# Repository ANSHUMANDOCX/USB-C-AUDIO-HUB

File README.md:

# USB C AUDIO + USB HUB

## About
This is a USB C HUB along with a Audio Out/In port. This design uses PCM2912A along with SL2.1A 

- It has 3 downstream USB-C ports and 1 USB-C input so we can connect any desired length of cable we want to use with it
- TRRS audio jack for headphones with integrated microphone along with a mute/unmute switch built into the hub 
## Usage guide
- using it is as simple as it can be you just need to plug into the single usb C on the side and connected it to your device there are no driver needed 
- It doesnt need any firmware flashing 
- Its compatible with windows and linux 
## Assembly guide
All you need to do is place the PCB at the base plate align the holes and place the Body on top of it and screw the two parts using M2.5x6 or M2.5x8 countersunk screws.
## Parts used 
- TRRS Audio port
- USB C ports 
- PCM2912A
- SL2.1A
## Features
- USB 2.0 Full-Speed audio interface
- Stereo DAC output for headphones
- Microphone input with bias supply
- Integrated USB hub for multiple downstream devices
## PCB SCHEMATIC AND CAD

## Build 

https://drive.google.com/file/d/1LVbVrCVM0A2IdHVQDUf04vvttPNs0SB3/view?usp=sharing

## BOM
| SL NO | DESCRIPTION                                                | SUPPLIER    | PRICE |
|------|------------------------------------------------------------|------------|-------|
| 1 | [LCSC BOM items](https://github.com/ANSHUMANDOCX/USB-C-AUDIO-HUB/blob/main/PCB/BOM.csv) | LCSC | $22 |
| 2 | PCB and Stencil | JLCPCB | $16 |
| 3 | Screws and Heatset Inserts | Only Screws | $2 |
|4| [Solder Paste](https://www.flipkart.com/babatools-rl-403-solder-paste-10cc-1-w-simple/p/itm13022305a7dd0?pid=SOIGP28DYHUXUUF6&lid=LSTSOIGP28DYHUXUUF6AXDR0B&marketplace=FLIPKART&cmpid=content_soldering-iron_23274603117_g_8965229628_gmc_pla&tgi=sem,1,G,11214002,g,search,,784823478926,,,,c,,,,,,,&&cmpid=content_23274603117_gmc_pla&gad_campaignid=23274603117) | Flipkart| 4$|
|  | **TOTAL** |  | **$44** |

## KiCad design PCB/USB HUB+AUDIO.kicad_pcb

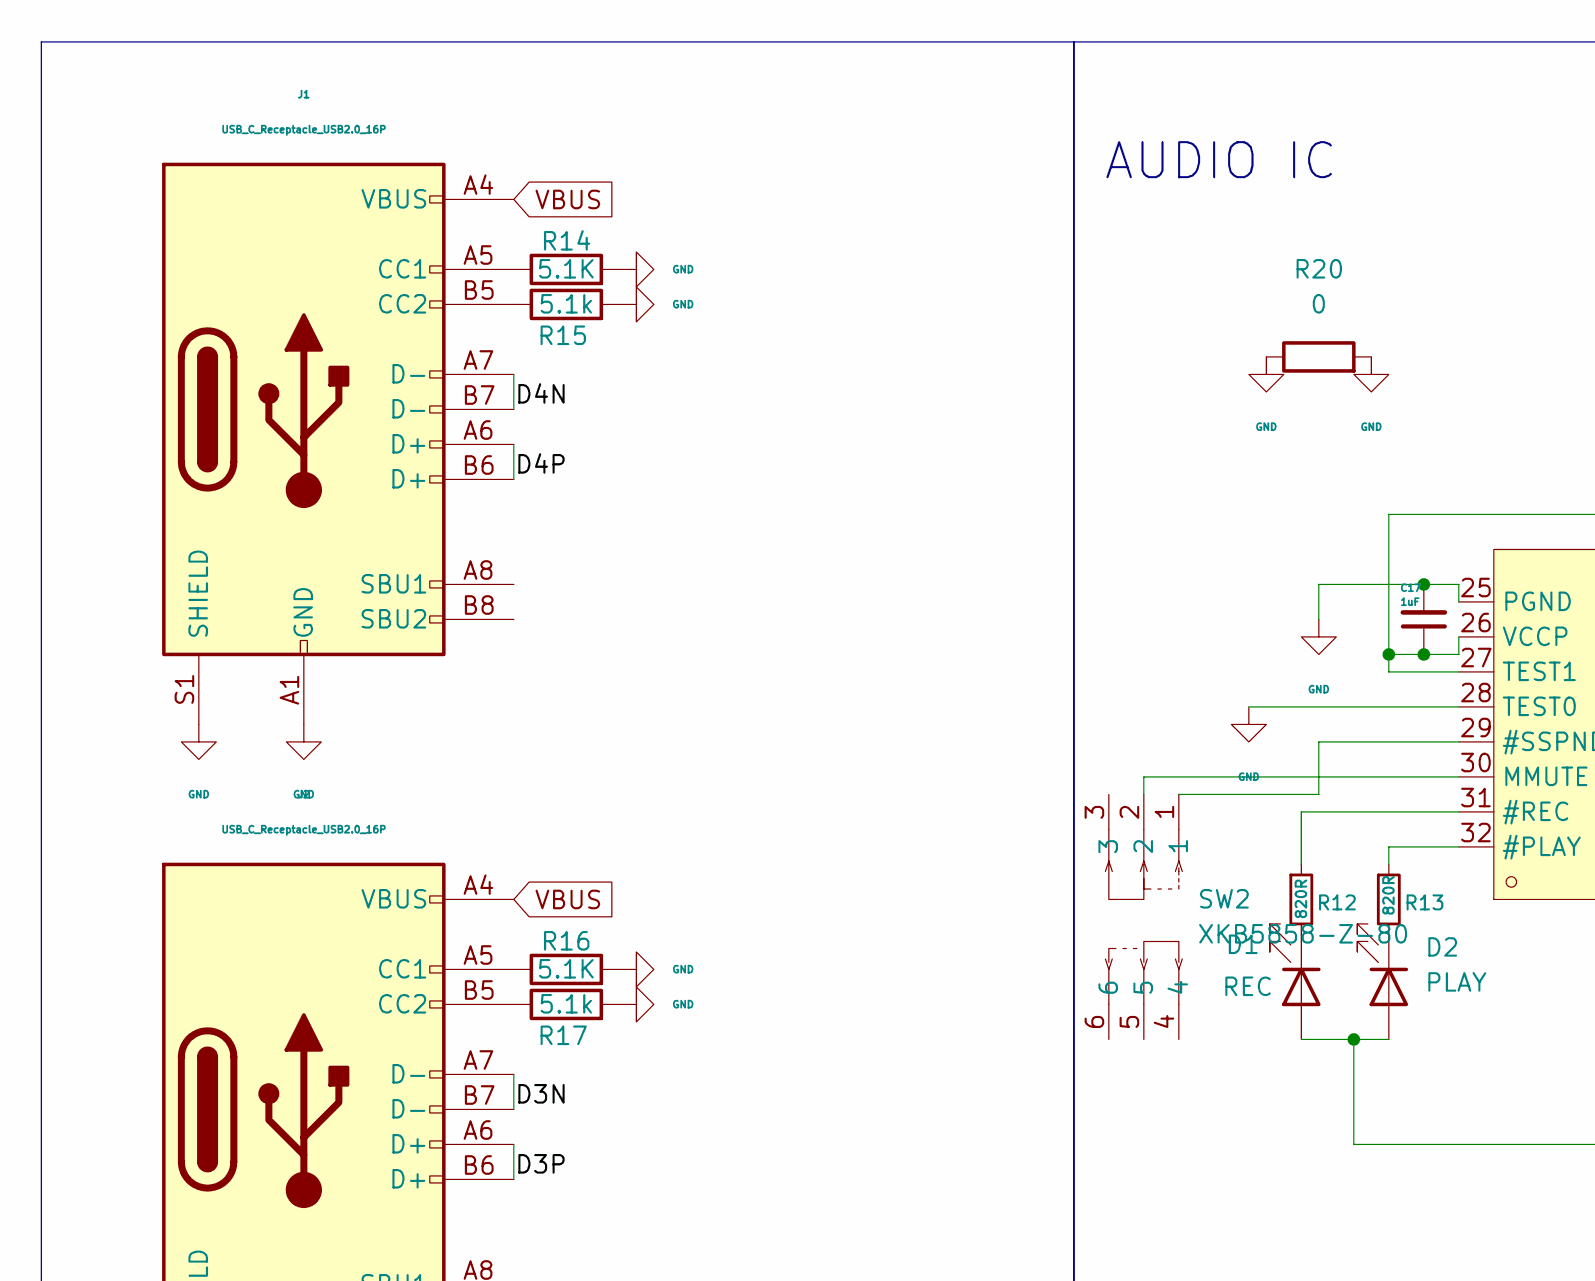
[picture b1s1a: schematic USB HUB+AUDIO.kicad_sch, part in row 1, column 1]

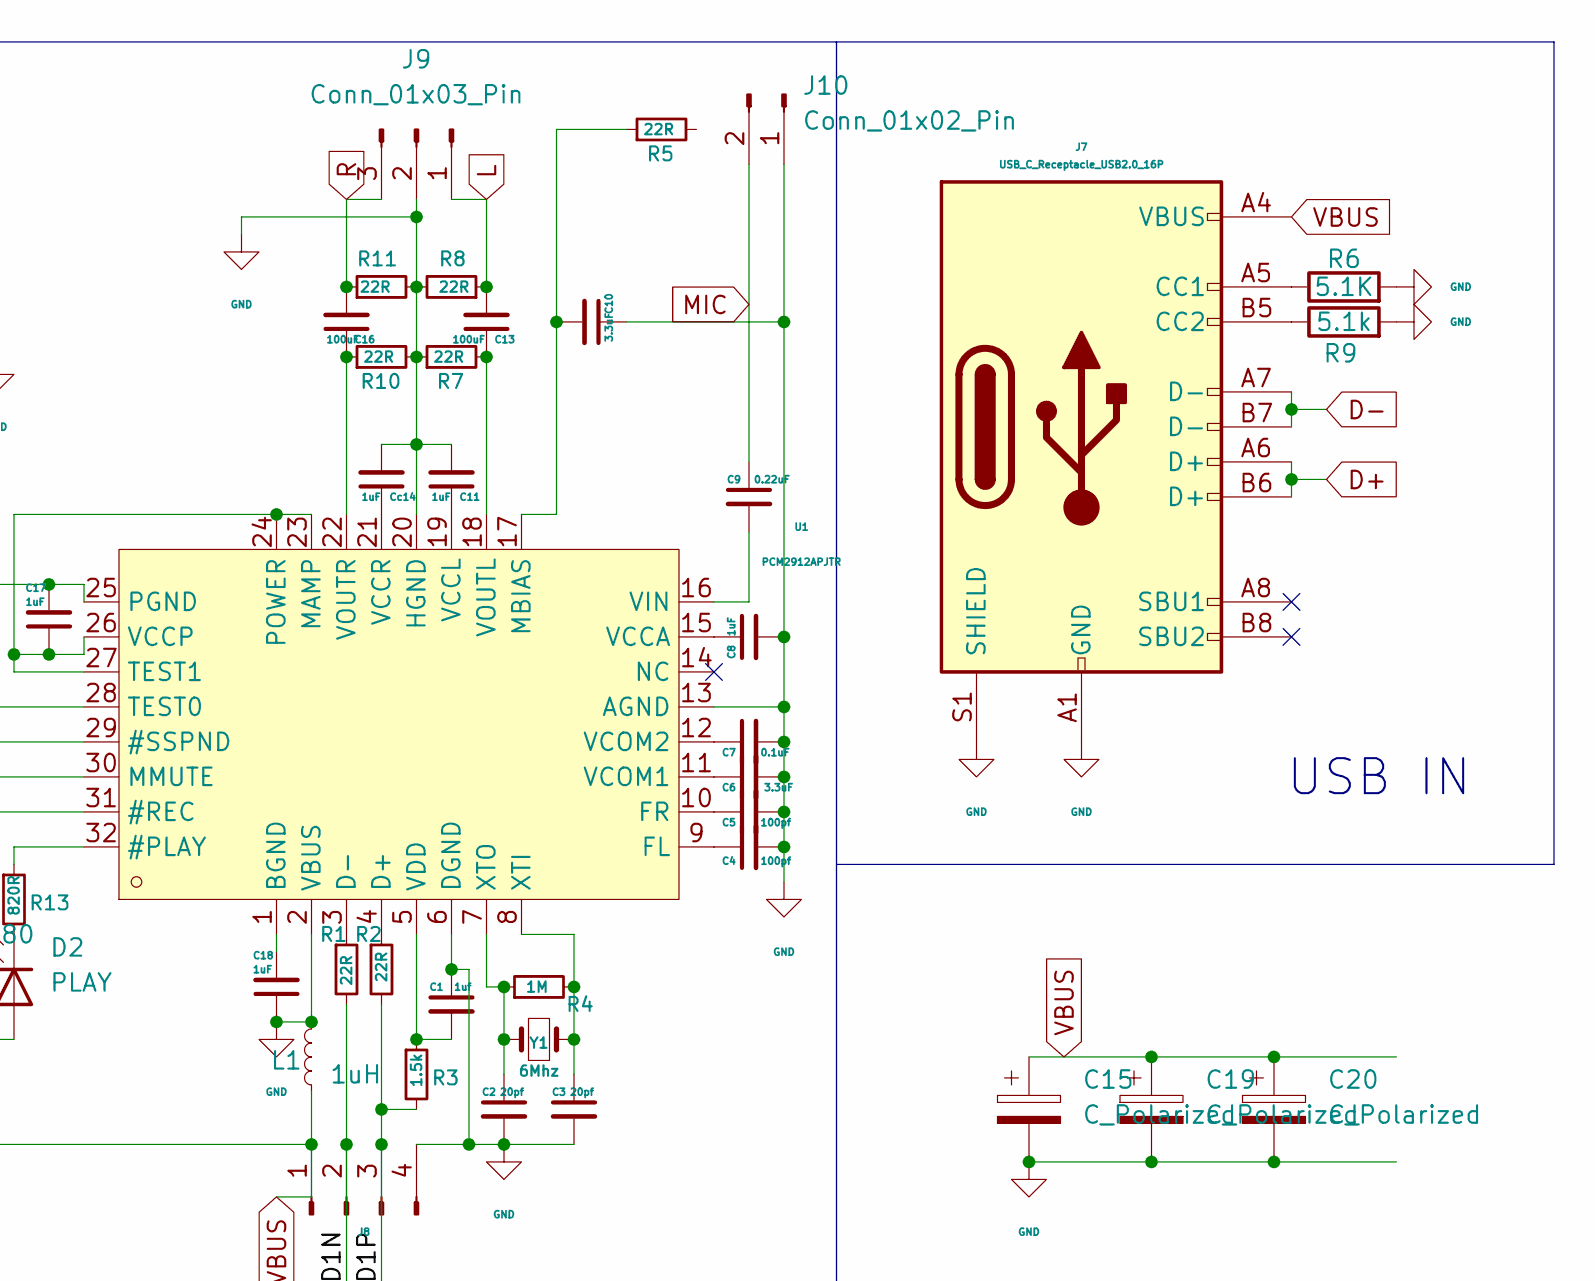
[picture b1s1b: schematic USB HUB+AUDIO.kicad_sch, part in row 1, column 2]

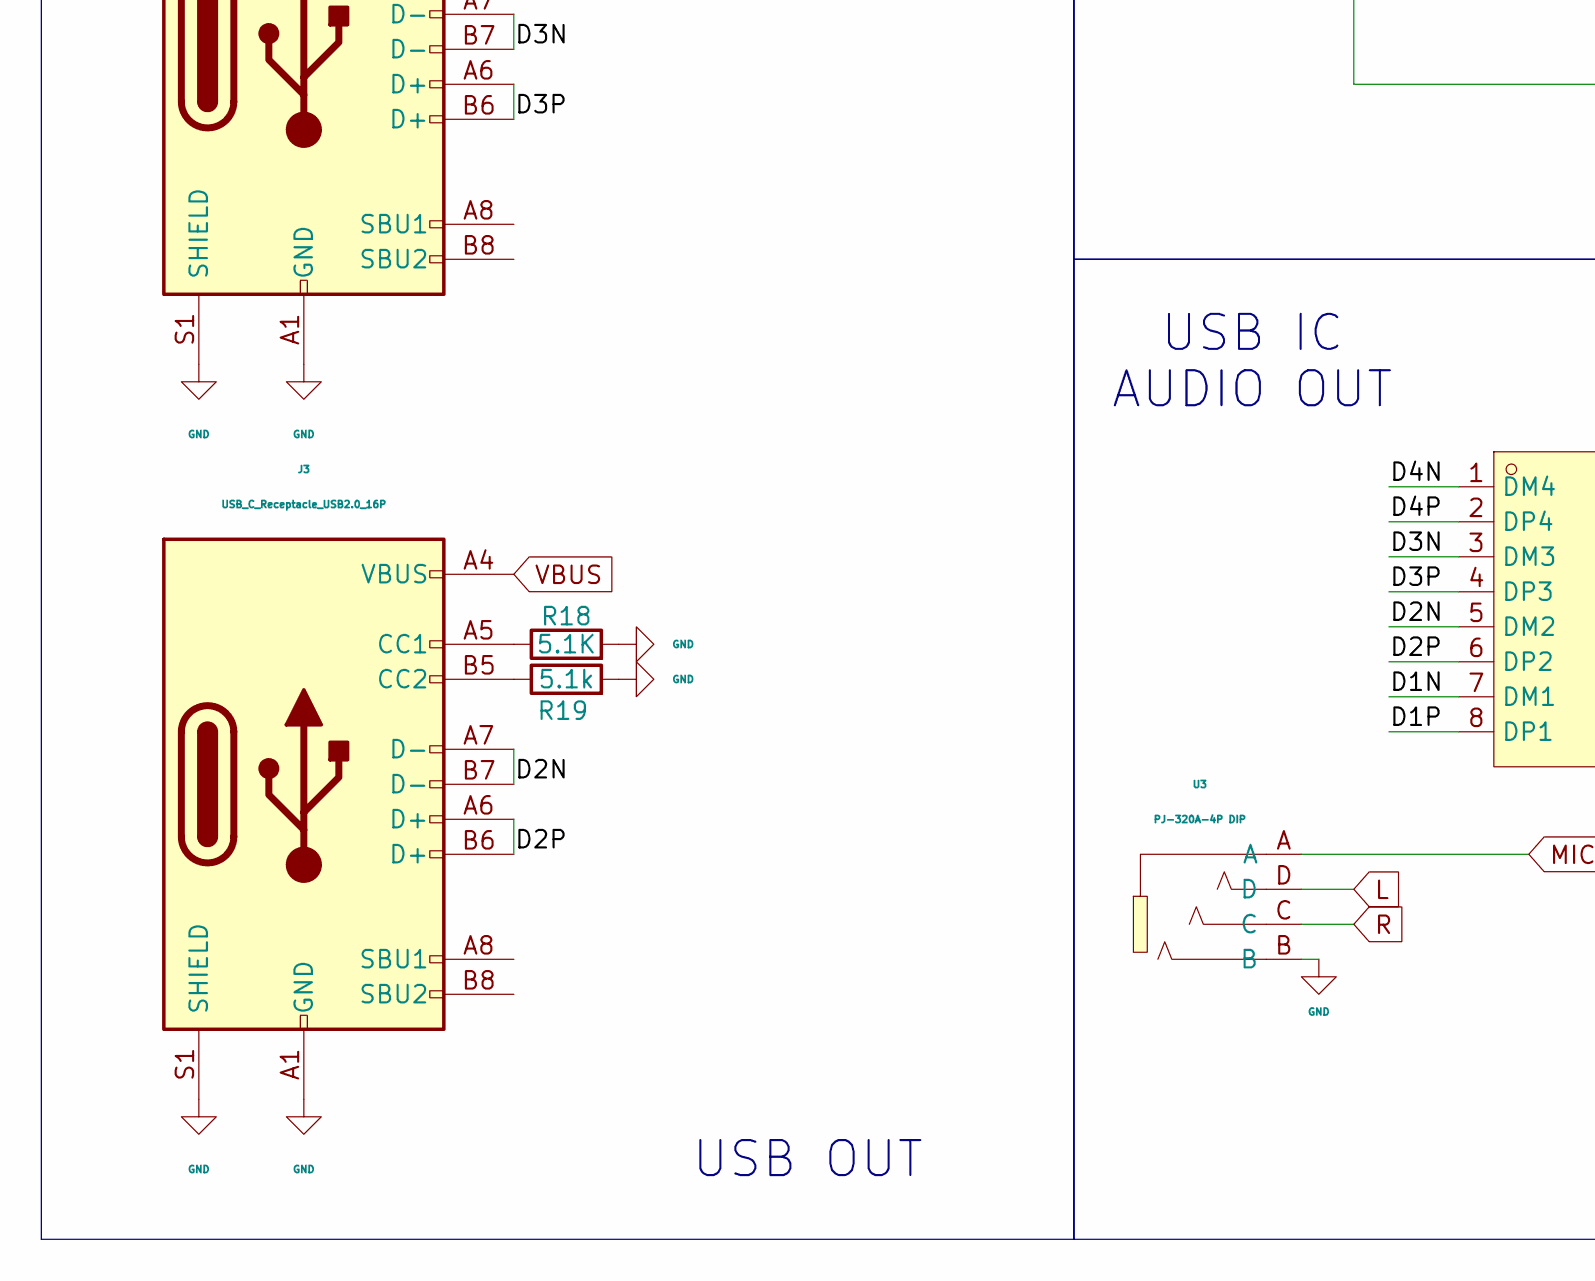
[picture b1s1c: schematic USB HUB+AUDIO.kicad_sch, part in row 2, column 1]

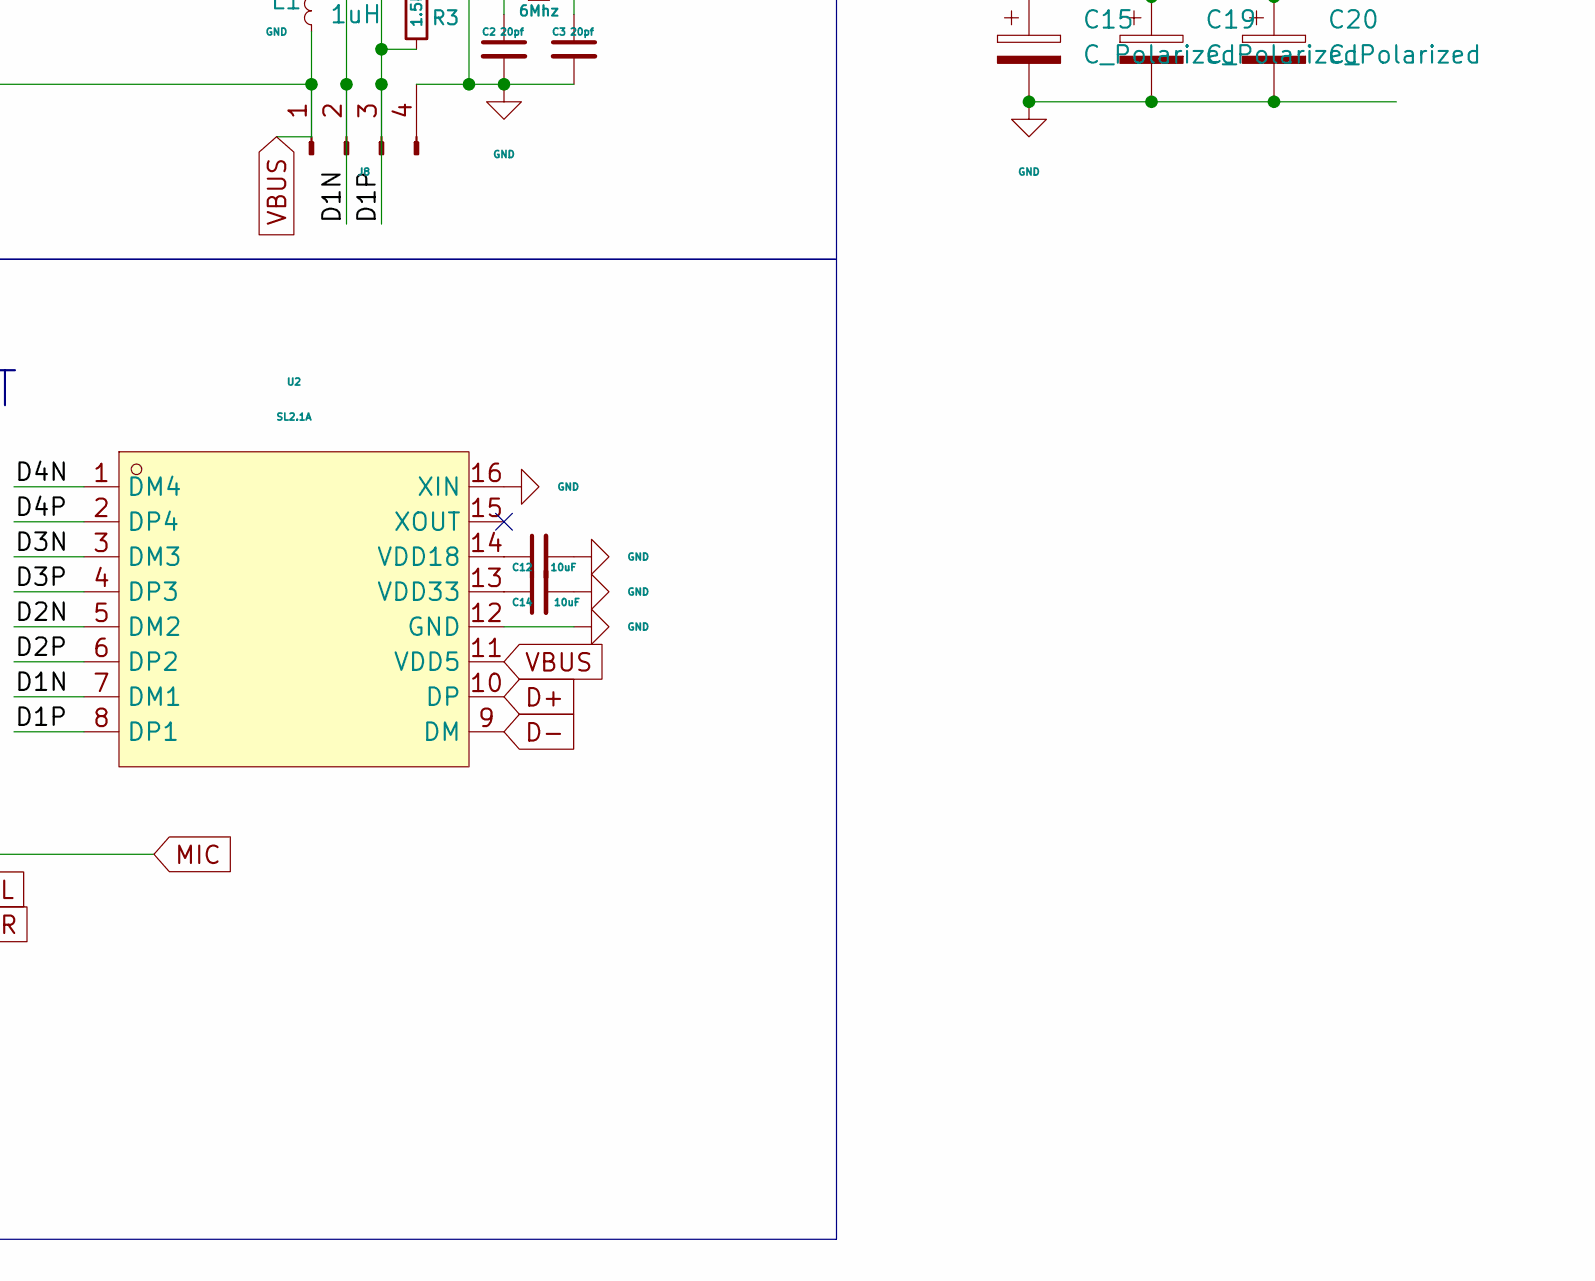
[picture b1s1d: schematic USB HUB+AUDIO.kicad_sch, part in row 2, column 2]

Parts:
C1: 1uf; C_0402_1005Metric_Pad0.74x0.62mm_HandSolder
C2, C3: 20pf; C_0402_1005Metric_Pad0.74x0.62mm_HandSolder
C4, C5: 100pf; C_0402_1005Metric_Pad0.74x0.62mm_HandSolder
C6, C10: 3.3uF; C_0402_1005Metric_Pad0.74x0.62mm_HandSolder
C7: 0.1uF; C_0402_1005Metric_Pad0.74x0.62mm_HandSolder
C8, C11, C17, C18: 1uF; C_0402_1005Metric_Pad0.74x0.62mm_HandSolder
C9: 0.22uF; C_0402_1005Metric_Pad0.74x0.62mm_HandSolder
C12, C14: 10uF; C_0402_1005Metric_Pad0.74x0.62mm_HandSolder
C13, C16: 100uF; CP_Elec_5x5.4
C15, C19, C20: C_Polarized; CP_EIA-3528-15_AVX-H
Cc14: 1uF; C_0402_1005Metric_Pad0.74x0.62mm_HandSolder
D1: REC; LED_0603_1608Metric
D2: PLAY; LED_0603_1608Metric
J1, J2, J3, J7: USB_C_Receptacle_USB2.0_16P; USB_C_Receptacle_GCT_USB4105-xx-A_16P_TopMnt_Horizontal
J8: Conn_01x04_Pin; PinHeader_1x04_P2.54mm_Vertical
J9: Conn_01x03_Pin; PinHeader_1x03_P2.54mm_Vertical
J10: Conn_01x02_Pin; PinHeader_1x02_P2.54mm_Vertical
L1: 1uH; L1008
R1, R2, R5, R7, R8, R10, R11: 22R; R_0402_1005Metric
R3: 1.5k; R_0402_1005Metric
R4: 1M; R_0402_1005Metric
R6, R14, R16, R18: 5.1K; R_0402_1005Metric
R9, R15, R17, R19: 5.1k; R_0402_1005Metric
R12, R13: 820R; R_0402_1005Metric
R20: 0; R_0805_2012Metric
SW2: XKB5858-Z-80; SW-TH_XKB5858-Z-80; LCSC Part C318866
U1: PCM2912APJTR; TQFP-32_L7.0-W7.0-P0.80-LS9.0-TL; LCSC Part C475497
U2: SL2.1A; SOP-16_L10.0-W3.9-P1.27-LS6.0-BL; LCSC Part C192893
U3: PJ-320A-4P DIP; AUDIO-TH_PJ-320A-4P-DIP; LCSC Part C18185602
Y1: 6Mhz; CRYSTAL-SMD_L7.0-W4.0-LS7.8

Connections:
/D1N: J8.2, R1.2, U2.7 (DM1)
/D1P: J8.3, R2.2, R3.2, U2.8 (DP1)
/D2N: J3.A7 (D-), J3.B7 (D-), U2.5 (DM2)
/D2P: J3.A6 (D+), J3.B6 (D+), U2.6 (DP2)
/D3N: J2.A7 (D-), J2.B7 (D-), U2.3 (DM3)
/D3P: J2.A6 (D+), J2.B6 (D+), U2.4 (DP3)
/D4N: J1.A7 (D-), J1.B7 (D-), U2.1 (DM4)
/D4P: J1.A6 (D+), J1.B6 (D+), U2.2 (DP4)
D+: J7.A6 (D+), J7.B6 (D+), U2.10 (DP)
D-: J7.A7 (D-), J7.B7 (D-), U2.9 (DM)
GND: C1.1, C2.2, C3.2, C4.2, C5.2, C6.2, C7.2, C8.2, C10.1, C11.2, C12.2, C14.2, C15.2, C17.2, C18.1, C19.2, C20.2, Cc14.2, J1.A1 (GND), J1.A12 (GND), J1.B1 (GND), J1.B12 (GND), J1.S1 (SHIELD), J2.A1 (GND), J2.A12 (GND), J2.B1 (GND), J2.B12 (GND), J2.S1 (SHIELD), J3.A1 (GND), J3.A12 (GND), J3.B1 (GND), J3.B12 (GND), J3.S1 (SHIELD), J7.A1 (GND), J7.A12 (GND), J7.B1 (GND), J7.B12 (GND), J7.S1 (SHIELD), J8.4, J9.2, J10.1, L1.2, R6.2, R7.1, R8.2, R9.2, R10.2, R11.2, R14.2, R15.2, R16.2, R17.2, R18.2, R19.2, R20.1, R20.2, U1.2 (VBUS), U1.6 (DGND), U1.13 (AGND), U1.20 (HGND), U1.25 (PGND), U1.28 (TEST0), U2.12 (GND), U2.16 (XIN), U3.B
L: C13.2, J9.1, R8.1, U3.D
MIC: C9.1, J10.2, U3.A
unnamed: D1.1 (K), R12.2
unnamed: D2.1 (K), R13.2
unnamed: J1.A5 (CC1), R14.1
unnamed: J1.B5 (CC2), R15.1
unnamed: J2.A5 (CC1), R16.1
unnamed: J2.B5 (CC2), R17.1
unnamed: J3.A5 (CC1), R18.1
unnamed: J3.B5 (CC2), R19.1
unnamed: J7.A5 (CC1), R6.1
unnamed: J7.B5 (CC2), R9.1
unnamed: R13.1, U1.32 (#PLAY)
unnamed: R12.1, U1.31 (#REC)
unnamed: SW2.1, U1.29 (#SSPND)
unnamed: C18.2, U1.1 (BGND)
unnamed: R2.1, U1.4 (D+)
unnamed: R1.1, U1.3 (D-)
unnamed: C4.1, U1.9 (FL)
unnamed: C5.1, U1.10 (FR)
unnamed: C17.1, U1.23 (MAMP), U1.24 (POWER), U1.26 (VCCP), U1.27 (TEST1)
unnamed: C10.2, R5.1, U1.17 (MBIAS)
unnamed: SW2.2, U1.30 (MMUTE)
unnamed: C8.1, U1.15 (VCCA)
unnamed: C11.1, U1.19 (VCCL)
unnamed: Cc14.1, U1.21 (VCCR)
unnamed: C6.1, U1.11 (VCOM1)
unnamed: C7.1, U1.12 (VCOM2)
unnamed: C1.2, R3.1, U1.5 (VDD)
unnamed: C9.2, U1.16 (VIN)
unnamed: C13.1, R7.2, U1.18 (VOUTL)
unnamed: C16.1, R10.1, U1.22 (VOUTR)
unnamed: C3.1, R4.2, U1.8 (XTI), Y1.2
unnamed: C2.1, R4.1, U1.7 (XTO), Y1.1
unnamed: C12.1, U2.14 (VDD18)
unnamed: C14.1, U2.13 (VDD33)
R: C16.2, J9.3, R11.1, U3.C
VBUS: C15.1, C19.1, C20.1, D1.2 (A), D2.2 (A), J1.A4 (VBUS), J1.A9 (VBUS), J1.B4 (VBUS), J1.B9 (VBUS), J2.A4 (VBUS), J2.A9 (VBUS), J2.B4 (VBUS), J2.B9 (VBUS), J3.A4 (VBUS), J3.A9 (VBUS), J3.B4 (VBUS), J3.B9 (VBUS), J7.A4 (VBUS), J7.A9 (VBUS), J7.B4 (VBUS), J7.B9 (VBUS), J8.1, L1.1, U2.11 (VDD5)

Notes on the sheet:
AUDIO IC
USB OUT
USB IN
USB IC AUDIO OUT

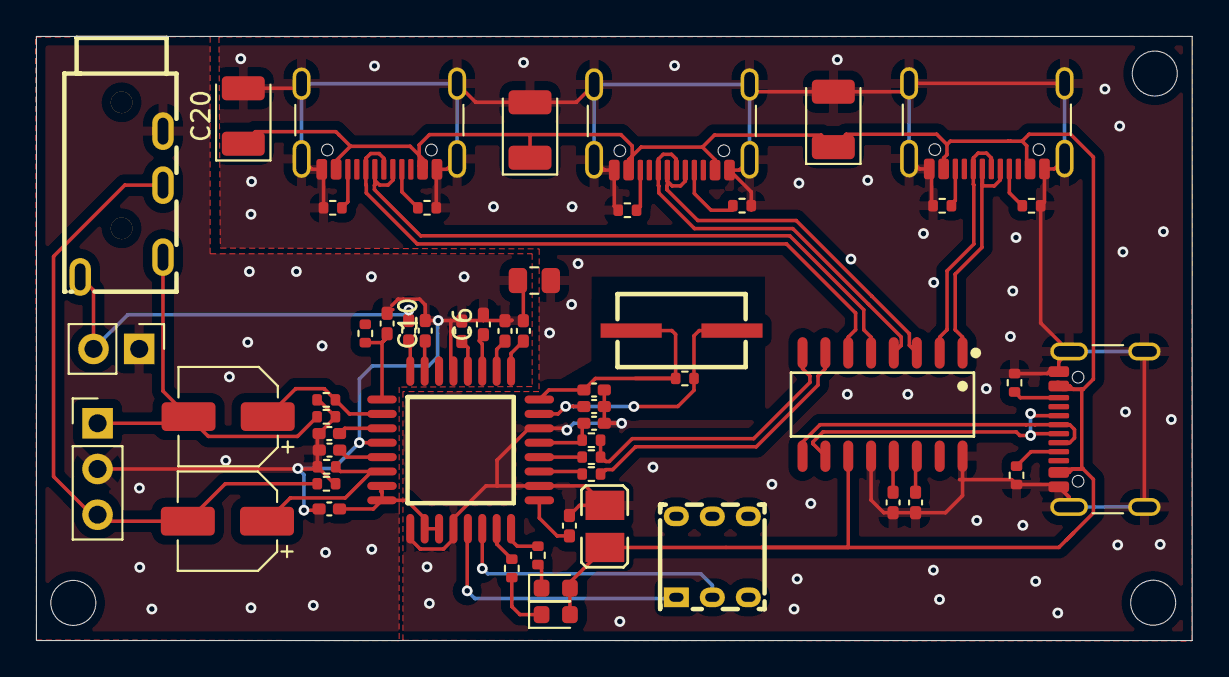
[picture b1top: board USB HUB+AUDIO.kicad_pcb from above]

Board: 2 copper layers, 64.2 x 33.6 mm, 55 parts (0 on the bottom side), 49 nets.

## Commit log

2026-03-10 Clarify USB C HUB features and usage instructions
    Updated the description of the USB C HUB to clarify the ports and usage instructions.
2026-06-10 Update README with build images and BOM section
    Added new images and build section to the README.
